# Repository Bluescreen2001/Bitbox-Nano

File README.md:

# Bitbox-Nano
This is an alternative PCB to makabuf's bitbox game console

## WARNING: this hardware has not been checked for functionality yet!!!

I want to use a special case for the console, so I created this version of the PCB.
I added an ESP32 which is also connected to the VGA signals and the STM32's SDWI interface lines. 
With this additions the ESP can program and debug the STM. It also can generate VGA signals, so hopefully you can also use the ESP VGA libs to generate video. You have to consoles in one device.

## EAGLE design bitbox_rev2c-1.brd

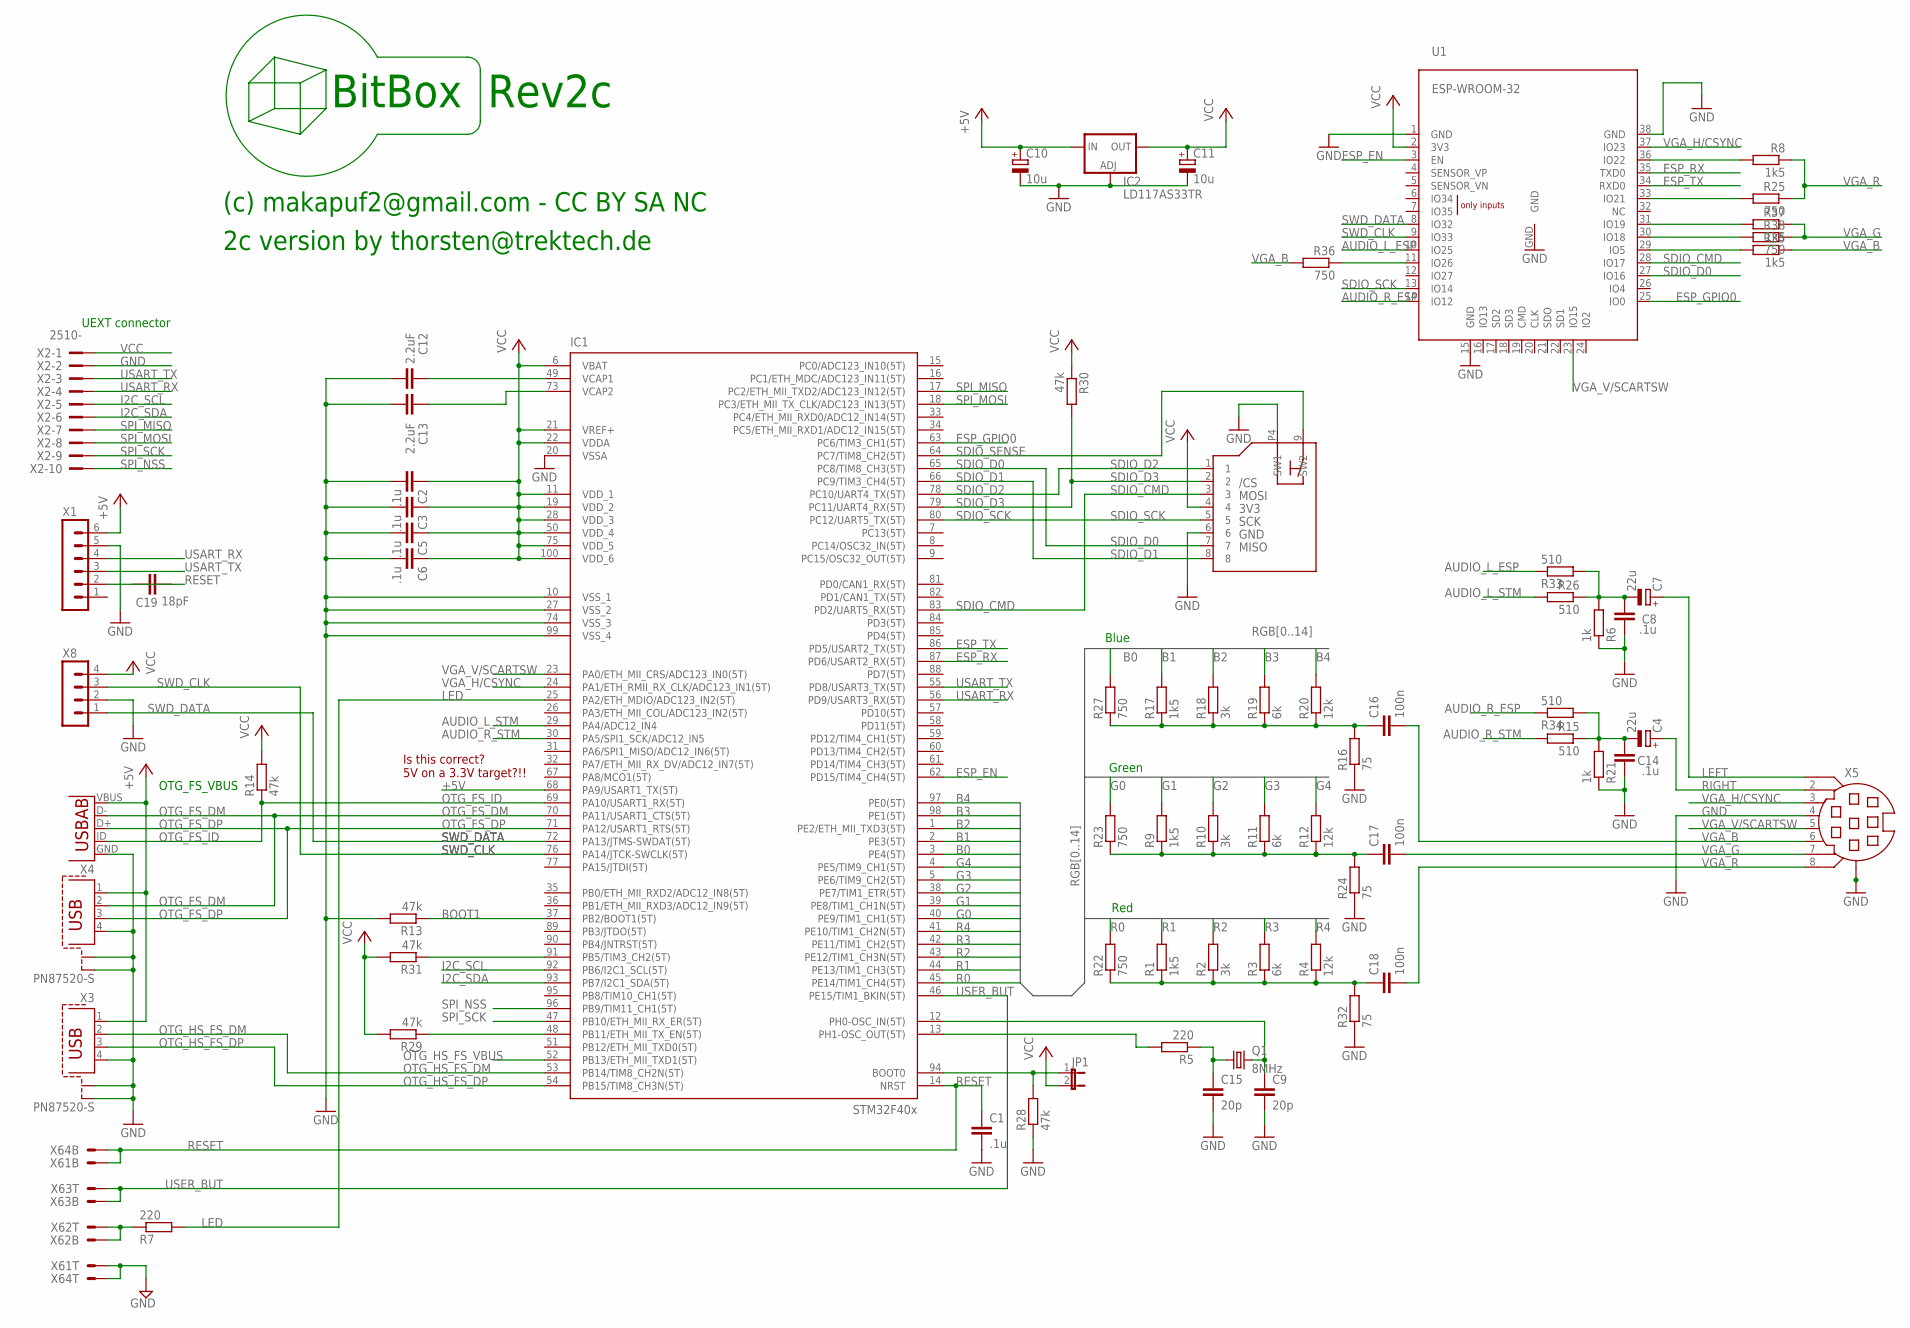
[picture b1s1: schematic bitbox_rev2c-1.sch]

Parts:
C1, C2, C3, C5, C6, C8, C14: .1u; C0805
C4, C7: 22u; 153CLV-0505
C9, C15: 20p; C0805
C10, C11: 10u; SMC_A
C12, C13: 2.2uF; C0805
C16, C17, C18: 100n; C0805
C19: 18pF; C0805
IC1: STM32F407V; TQFP100
IC2: LD117AS33TR; SOT223
J1: MICROSD-SWITCH; MICROSD-ATOM
JP1: JP1E; JP1
Q1: 8MHz; SM49
R1, R8, R9, R17, R35, R37: 1k5; R0805
R2, R10, R18: 3k; R0805
R3, R11, R19: 6k; R0805
R4, R12, R20: 12k; R0805
R5, R7: 220; R0805
R6, R21: 1k; R0805
R13, R14, R28, R29, R30, R31: 47k; R0805
R15, R26, R33, R34: 510; R0805
R16, R24, R32: 75; R0805
R22, R23, R25, R27, R36, R38: 750; R0805
U1: ESP-WROOM-32
X1: MA06-1
X2: 2510-; PAK100/2500-10
X3, X4: PN87520-S
X5: MINI-DIN-8
X6: PCB_CONNECTOR_4X2; PCB_CONNECTOR_2X4POL
X7: USB-AB; USB-AB-MICRO-SMD
X8: MA04-1

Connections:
+5V: C10.+, IC1.68 (PA9/USART1_TX(5T)), IC2.3 (IN), X1.6, X3.1, X4.1, X7.VBUS
AUDIO_L: C7.-, C8.1, R6.2, R26.1, R33.2
AUDIO_L_ESP: R33.1, U1.10 (IO25)
AUDIO_L_STM: IC1.29 (PA4/ADC12_IN4), R26.2
AUDIO_R: C4.-, C14.1, R15.1, R21.2, R34.2
AUDIO_R_ESP: R34.1, U1.14 (IO12)
AUDIO_R_STM: IC1.30 (PA5/SPI1_SCK/ADC12_IN5), R15.2
B0: IC1.3 (PE4(5T)), R27.2
B1: IC1.2 (PE3(5T)), R17.2
B2: IC1.1 (PE2/ETH_MII_TXD3(5T)), R18.2
B3: IC1.98 (PE1(5T)), R19.2
B4: IC1.97 (PE0(5T)), R20.2
BOOT1: IC1.37 (PB2/BOOT1(5T)), R13.1
ESP_EN: IC1.62 (PD15/TIM4_CH4(5T)), U1.3 (EN)
ESP_GPIO0: IC1.63 (PC6/TIM3_CH1(5T)), U1.25 (IO0)
ESP_RX: IC1.87 (PD6/USART2_RX(5T)), U1.35 (TXD0)
ESP_TX: IC1.86 (PD5/USART2_TX(5T)), U1.34 (RXD0)
G0: IC1.40 (PE9/TIM1_CH1(5T)), R23.2
G1: IC1.39 (PE8/TIM1_CH1N(5T)), R9.2
G2: IC1.38 (PE7/TIM1_ETR(5T)), R10.2
G3: IC1.5 (PE6/TIM9_CH2(5T)), R11.2
G4: IC1.4 (PE5/TIM9_CH1(5T)), R12.2
GND: C1.2, C2.2, C3.2, C5.2, C6.2, C8.2, C9.2, C10.-, C11.-, C12.2, C13.2, C14.2, C15.2, IC1.10 (VSS_1), IC1.20 (VSSA), IC1.27 (VSS_2), IC1.74 (VSS_3), IC1.99 (VSS_4), IC2.1 (ADJ), J1.6, J1.P4 (SW1), R6.1, R13.2, R16.1, R21.1, R24.1, R28.1, R32.1, U1.1 (GND), U1.15 (GND), U1.38 (GND), U1.GND, X1.5, X2.2, X3.4, X3.S1, X3.S2, X4.4, X4.S1, X4.S2, X5.4, X5.G (G1), X6.1T, X6.4T, X7.GND, X8.2
I2C_SCL: IC1.92 (PB6/I2C1_SCL(5T)), X2.5
I2C_SDA: IC1.93 (PB7/I2C1_SDA(5T)), X2.6
LED: IC1.25 (PA2/ETH_MDIO/ADC123_IN2(5T)), R7.2
LEFT: C7.+, X5.1
unnamed: C19.2, X1.2
unnamed: C13.1, IC1.73 (VCAP2)
unnamed: C16.1, R16.2, R17.1, R18.1, R19.1, R20.1, R27.1
unnamed: C12.1, IC1.49 (VCAP1)
unnamed: R8.2, U1.36 (IO22)
unnamed: C15.1, Q1.1, R5.1
unnamed: C9.1, IC1.12 (PH0-OSC_IN(5T)), Q1.2
unnamed: C17.1, R9.1, R10.1, R11.1, R12.1, R23.1, R24.2
unnamed: R25.2, U1.33 (IO21)
unnamed: IC1.91 (PB5/TIM3_CH2(5T)), R31.1
unnamed: R37.2, U1.31 (IO19)
unnamed: IC1.13 (PH1-OSC_OUT(5T)), R5.2
unnamed: IC1.94 (BOOT0), JP1.1, R28.2
unnamed: R38.2, U1.30 (IO18)
unnamed: R35.2, U1.29 (IO5)
unnamed: R7.1, X6.2B, X6.2T
unnamed: C18.1, R1.1, R2.1, R3.1, R4.1, R22.1, R32.2
unnamed: R36.1, U1.11 (IO26)
OTG_FS_DM: IC1.70 (PA11/USART1_CTS(5T)), X4.2, X7.D-
OTG_FS_DP: IC1.71 (PA12/USART1_RTS(5T)), X4.3, X7.D+
OTG_FS_ID: IC1.69 (PA10/USART1_RX(5T)), R14.1, X7.ID (USBID)
OTG_HS_FS_DM: IC1.53 (PB14/TIM8_CH2N(5T)), X3.2
OTG_HS_FS_DP: IC1.54 (PB15/TIM8_CH3N(5T)), X3.3
OTG_HS_FS_VBUS: IC1.52 (PB13/ETH_MII_TXD1(5T))
R0: IC1.45 (PE14/TIM1_CH4(5T)), R22.2
R1: IC1.44 (PE13/TIM1_CH3(5T)), R1.2
R2: IC1.43 (PE12/TIM1_CH3N(5T)), R2.2
R3: IC1.42 (PE11/TIM1_CH2(5T)), R3.2
R4: IC1.41 (PE10/TIM1_CH2N(5T)), R4.2
RESET: C1.1, C19.1, IC1.14 (NRST), X6.1B, X6.4B
RIGHT: C4.+, X5.2
SDIO_CMD: IC1.83 (PD2/UART5_RX(5T)), J1.3, U1.28 (IO17)
SDIO_D0: IC1.65 (PC8/TIM8_CH3(5T)), J1.7, U1.27 (IO16)
SDIO_D1: IC1.66 (PC9/TIM3_CH4(5T)), J1.8
SDIO_D2: IC1.78 (PC10/UART4_TX(5T)), J1.1
SDIO_D3: IC1.79 (PC11/UART4_RX(5T)), J1.2, R30.2
SDIO_SCK: IC1.80 (PC12/UART5_TX(5T)), J1.5, U1.13 (IO14)
SDIO_SENSE: IC1.64 (PC7/TIM8_CH2(5T)), J1.9 (SW2)
SPI_MISO: IC1.17 (PC2/ETH_MII_TXD2/ADC123_IN12(5T)), X2.7
SPI_MOSI: IC1.18 (PC3/ETH_MII_TX_CLK/ADC123_IN13(5T)), X2.8
SPI_NSS: IC1.96 (PB9/TIM11_CH1(5T)), X2.10
SPI_SCK: IC1.47 (PB10/ETH_MII_RX_ER(5T)), X2.9
SWD_CLK: IC1.76 (PA14/JTCK-SWCLK(5T)), U1.9 (IO33), X8.3
SWD_DATA: IC1.72 (PA13/JTMS-SWDAT(5T)), U1.8 (IO32), X8.1
USART_RX: IC1.56 (PD9/USART3_RX(5T)), X1.4, X2.4
USART_TX: IC1.55 (PD8/USART3_TX(5T)), X1.3, X2.3
USER_BUT: IC1.46 (PE15/TIM1_BKIN(5T)), X6.3B, X6.3T
VCC: C2.1, C3.1, C5.1, C6.1, C11.+, IC1.6 (VBAT), IC1.11 (VDD_1), IC1.19 (VDD_2), IC1.21 (VREF+), IC1.22 (VDDA), IC1.28 (VDD_3), IC1.50 (VDD_4), IC1.75 (VDD_5), IC1.100 (VDD_6), IC2.2 (OUT), IC2.4 (OUT), J1.4, JP1.2, R14.2, R29.2, R30.1, R31.2, U1.2 (3V3), X2.1, X8.4
VGA_B: C16.2, R35.1, R36.2, X5.6
VGA_G: C17.2, R37.1, R38.1, X5.7
VGA_H/CSYNC: IC1.24 (PA1/ETH_RMII_RX_CLK/ADC123_IN1(5T)), U1.37 (IO23), X5.3
VGA_R: C18.2, R8.1, R25.1, X5.8
VGA_V/SCARTSW: IC1.23 (PA0/ETH_MII_CRS/ADC123_IN0(5T)), U1.23 (IO15), X5.5
YYY: IC1.48 (PB11/ETH_MII_TX_EN(5T)), R29.1

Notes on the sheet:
Red
Green
Blue
UEXT connector
OTG_FS_VBUS
BitBox Rev2c
(c) makapuf2@gmail.com - CC BY SA NC
2c version by thorsten@trektech.de
Is this correct? 5V on a 3.3V target?!!

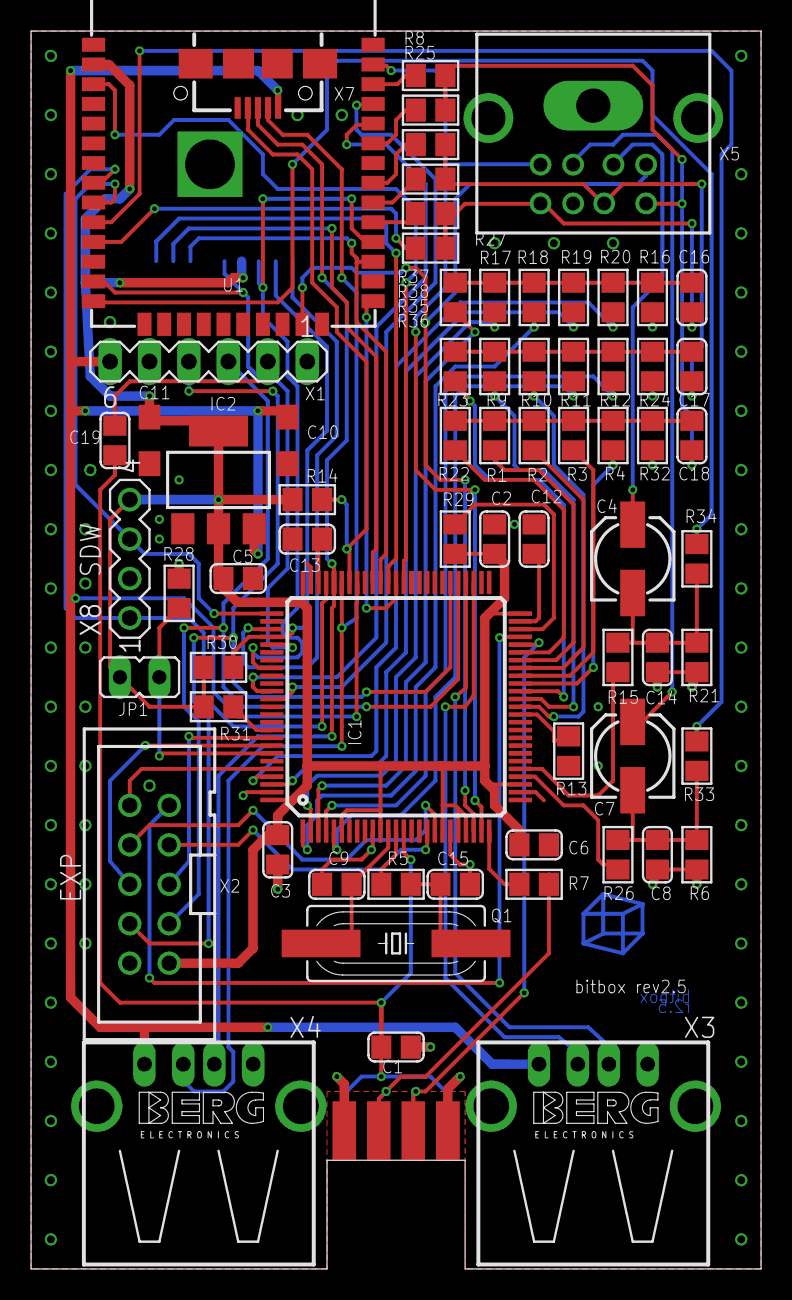
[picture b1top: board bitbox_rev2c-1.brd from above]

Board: 2 copper layers, 47.0 x 79.7 mm, 71 parts (1 on the bottom side), 80 nets.

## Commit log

2023-10-04 New README.md
    Edit Readme
2023-10-04 Add files via upload
    Initial commit

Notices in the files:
parts and their libraries:
SparkFun-Connectors: Licensing: CC v3.0 Share-Alike You are welcome to use this library for commercial purposes.
